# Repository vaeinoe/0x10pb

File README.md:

# 0x10pb

## What?

Yet another MIDI CC controller in 200x75mm footprint. 16 potentiometers x 4 banks. USB-C for flashing and MIDI device communication, hardware TRS MIDI type A output. Option for battery power.

MIDI CCs, channels and scaling per knob for all the four banks are programmable in the firmware (not on the fly via SysEx, at least not yet). Sends identical messages via both USB and TRS.

## Why?

There are many small DIY MIDI controllers more refined than this one, but I wanted something to use with battery-powered portable electronic instruments like the Dirtywave M8 and Teenage Engineering OP-1 Field, and

 1. I couldn't find anything that was battery powered and with both USB and hardware serial MIDI output. It's kind of a letdown to have a portable instrument with an internal battery and then have to carry around a power bank just for an auxiliary controller. Especially as most of these instruments don't act as USB hosts so you can't even power controllers directly from them.
 2. Most of the simple controllers are missing any kind of bank / page system. Quite often you want to control more than 16 parameters without remapping, but don't need to control them all at the same time.

Then a friend wanted one like this too for similar reasons, so I had to actually design one.

## How?

There's not much to it. A custom carrier board with a power switch, a bank button, two LEDs that indicate which bank is active (00, 01, 10, 11), TRS MIDI port and associated circuitry, and 16 pots read via a single multiplexer.

[Adafruit Feather RP2040](https://learn.adafruit.com/adafruit-feather-rp2040-pico) is used as the brain. Mainly because it conveniently has both a USB-C port and battery power / charging circuit built in.

### Hardware

First you'll need to get a carrier PCB. KiCad project and Gerbers are included for ordering your own. Once you have that, here's a list of parts you'll need to populate the board:

 - Adafruit Feather RP2040 plus suitable headers (eg. Adafruit slim ones): PCB will likely work with almost any Feather but you may need to modify pin mapping and use a different core lib
 - Optional: 3.7V LiPoly battery with Feather compatible (JST-PH) connector - I use a tiny 500mA one
 - U1: CD74HC4067M (SOIC)
 - U2: 74LVC1G07 (SOT-23-5 / SOT-25)
 - D1-D2: 3mm LED (Whichever you want, I used low power green ones)
 - J3: CUI SJ1-3523N TRS jack
 - C1-C2: 100nF 0603 capacitors
 - R1: 30R 0603 resistor
 - R2: 10R 0603 resistor
 - R3: 10k 0603 resistor
 - R4-R5: 0603 LED series resistors - calculate for your LEDs and 3.3V supply voltage, I used 330R
 - SW1: SPST Subminiature switch (5mm leg spacing)
 - SW2: Omron B3F-10xx series tactile switch + cap
 - RV1-RV16: 10k standard 9mm footprint potentiometers, eg. Alpha 9mm, plus relatively slim knobs such as Davies 1900h clones

If you can (hand) solder SOIC and 0603, populating the board is going to be fast and straightforward. Just mind the build order - SMT components first, and if you don't use removable headers for the Feather you might want to solder the pots before that so the Feather won't get in the way. Oh, and mind the SPST power switch polarity if you actually want "power off" to be on the left and "power on" on the right...

The repository includes a simple "sandwich" type panel design. If you use that, you'll also need some M3 spacers and screws. The exact height will depend on eg. how you mount the Feather. Try eg. 6x 10-12mm male-female ones for the front side (just attaching the panel using pots and power switch is OK too), 6x 17-18mm female-female ones for the back, plus 12x short screws to put it together. 

If you use removable header stack for the Feather, you may also want to secure the board in place with a short M2.5 spacer / screw and nut. Otherwise it may slip off during weeks / months / years of use.

For keeping the battery in place, use something like 3M Dual Lock or generic velcro to attach it to the bottom of the PCB or bottom panel. That way you can actually remove and replace the battery if you need to, but it won't move around.

### Firmware + bank mappings

Firmware can be edited and flashed with [Arduino IDE](https://www.arduino.cc/en/software). You'll also need to install these libraries (see instructions in respective repositories):

 - Earle F. Philhower, III's [Raspberry Pi Pico Arduino core](https://github.com/earlephilhower/arduino-pico)
 - Forty Seven Effects' [Arduino MIDI library](https://github.com/FortySevenEffects/arduino_midi_library)

After you have the IDE and the libraries installed, open the included Arduino sketch. In Tools menu, select "Adafruit Feather RP2040" as the board and "Adafruit TinyUSB" as the USB stack. Other options can be left as is. Then attach the USB-C cable to the Feather and turn power on. You should now be able to upload the sketch to the Feather via USB.

If the device isn't automatically recognized and you get an upload error, you may have to keep the "bootsel" button (in the back end of the board) pressed, quickly press "reset" towards the front of the board and finally release "bootsel" to get the board to bootloader mode. Then try uploading again.

The sketch also includes the hardcoded MIDI CC mappings for all the four banks. For now, whenever you want to edit the mappings, edit the source file according to instructions in the comments, then upload a new version to the Feather.

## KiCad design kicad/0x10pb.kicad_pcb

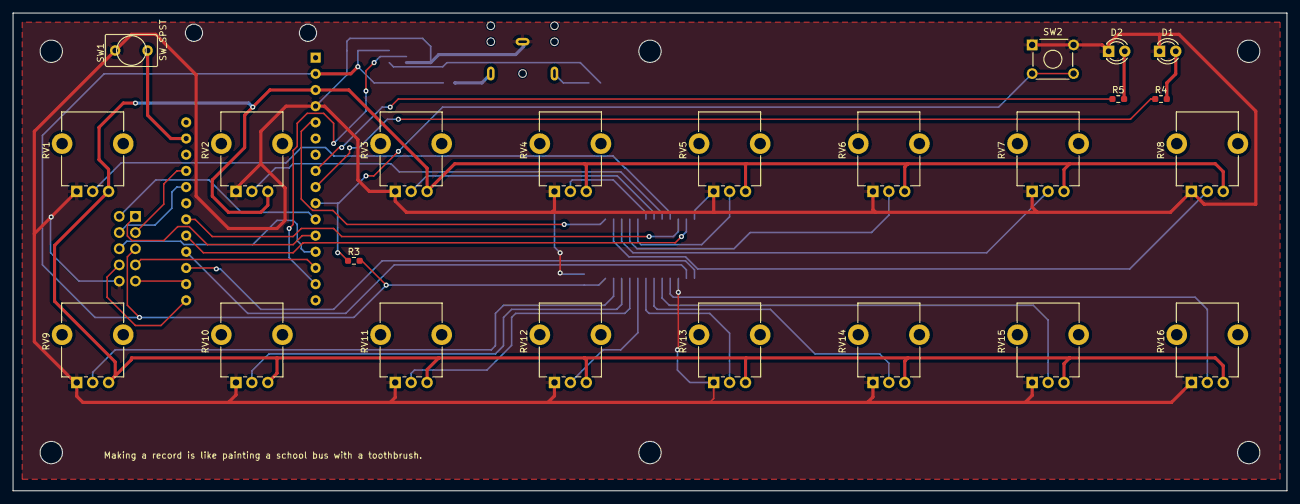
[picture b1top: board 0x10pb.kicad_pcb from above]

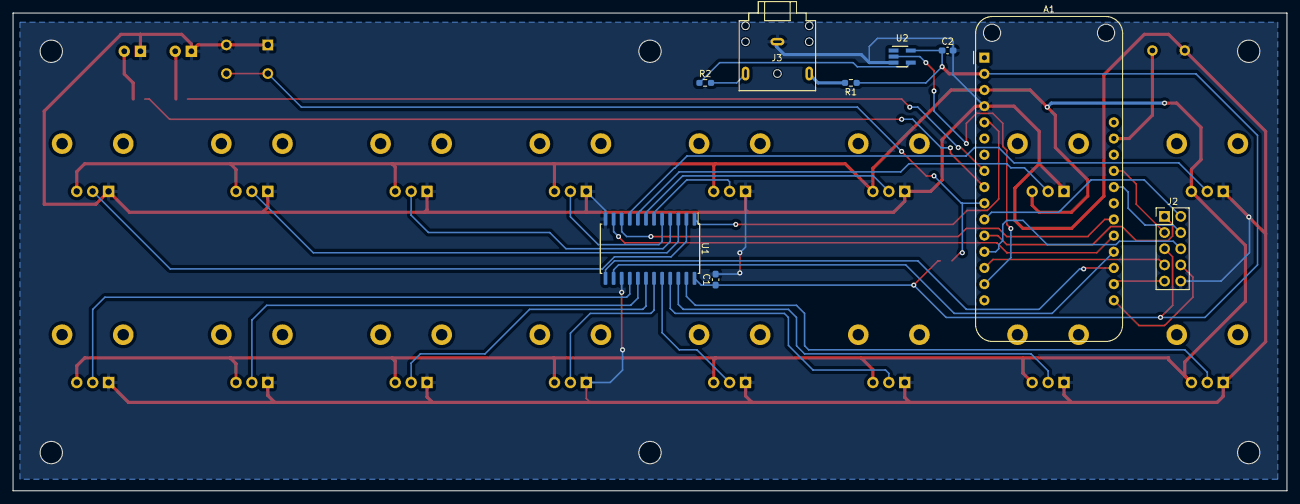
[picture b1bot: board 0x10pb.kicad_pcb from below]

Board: 2 copper layers, 200.0 x 75.0 mm, 32 parts (9 on the bottom side), 42 nets.

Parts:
A1: Adafruit_Feather_Generic; Adafruit_Feather
C1, C2: 100nF; C_0603_1608Metric_Pad1.08x0.95mm_HandSolder
D1, D2: LED; LED_D3.0mm
J2: Conn_02x05_Top_Bottom; PinHeader_2x05_P2.54mm_Vertical
J3: AudioJack3; Jack_3.5mm_CUI_SJ1-3523N_Horizontal
R1: 30R; R_0603_1608Metric_Pad0.98x0.95mm_HandSolder
R2: 10R; R_0603_1608Metric_Pad0.98x0.95mm_HandSolder
R3: 10k; R_0603_1608Metric_Pad0.98x0.95mm_HandSolder
R4, R5: 68R; R_0603_1608Metric_Pad0.98x0.95mm_HandSolder
RV1, RV2, RV3, RV4, RV5, RV6, RV7, RV8, RV9, RV10, RV11, RV12, RV13, RV14, RV15, RV16: R_Potentiometer; Potentiometer_Alpha_RD901F-40-00D_Single_Vertical_CircularH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
SW1: SW_SPST; Switch_Toggle_SPST_SubMini
SW2: SW_Push; SW_TH_Tactile_Omron_B3F-10xx
U1: CD74HC4067M; SOIC-24W_7.5x15.4mm_P1.27mm
U2: 74LVC1G07; SOT-23-5_HandSoldering

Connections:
+3.3V: A1.2 (3V3), C1.1, C2.1, J2.5, R1.1, R3.2, U1.24 (VCC), U2.5 (VCC)
+3.3VA: A1.3 (AREF), RV1.3, RV2.3, RV3.3, RV4.3, RV5.3, RV6.3, RV7.3, RV8.3, RV9.3, RV10.3, RV11.3, RV12.3, RV13.3, RV14.3, RV15.3, RV16.3
GND: A1.4 (GND), C1.2, C2.2, D1.1 (K), D2.1 (K), J2.10, J3.S, RV1.1, RV2.1, RV3.1, RV4.1, RV5.1, RV6.1, RV7.1, RV8.1, RV9.1, RV10.1, RV11.1, RV12.1, RV13.1, RV14.1, RV15.1, RV16.1, SW1.1 (A), SW2.1, U1.12 (GND), U1.15 (~E), U2.3 (GND)
unnamed: A1.5 (A0), U1.1 (COM)
unnamed: A1.8 (A3), R5.1
unnamed: A1.9 (A4), R4.1
unnamed: A1.10 (A5), R3.1, SW2.2
unnamed: A1.19 (D0), U1.13 (S3)
unnamed: A1.20 (D1), U1.14 (S2)
unnamed: A1.21 (D2), U1.11 (S1)
unnamed: A1.22 (D3), U1.10 (S0)
unnamed: A1.24 (D5), J2.4
unnamed: A1.25 (D6), J2.3
unnamed: A1.27 (EN), SW1.2 (B)
unnamed: A1.13 (MISO), J2.6
unnamed: A1.12 (MOSI), J2.1
unnamed: A1.14 (RX), J2.7
unnamed: A1.11 (SCK), J2.2
unnamed: A1.18 (SCL), J2.9
unnamed: A1.17 (SDA), J2.8
unnamed: A1.15 (TX), U2.2
unnamed: D1.2 (A), R4.2
unnamed: D2.2 (A), R5.2
unnamed: J3.R, R1.2
unnamed: J3.T, R2.2
unnamed: R2.1, U2.4
unnamed: RV1.2, U1.9 (I0)
unnamed: RV2.2, U1.8 (I1)
unnamed: RV3.2, U1.7 (I2)
unnamed: RV4.2, U1.6 (I3)
unnamed: RV5.2, U1.5 (I4)
unnamed: RV6.2, U1.4 (I5)
unnamed: RV7.2, U1.3 (I6)
unnamed: RV8.2, U1.2 (I7)
unnamed: RV9.2, U1.23 (I8)
unnamed: RV10.2, U1.22 (I9)
unnamed: RV11.2, U1.21 (I10)
unnamed: RV12.2, U1.20 (I11)
unnamed: RV13.2, U1.19 (I12)
unnamed: RV14.2, U1.18 (I13)
unnamed: RV15.2, U1.17 (I14)
unnamed: RV16.2, U1.16 (I15)

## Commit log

2024-03-29 Add instructions, board and panel files and code
2024-03-29 Minor README update
2024-03-29 Create LICENSE
